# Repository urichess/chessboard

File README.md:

# chessboard

tests of chessboard using arduino + zephyr

Interesting links

Proyectos y tecnologías clave que te pueden ayudar
1. lichess-bot

https://github.com/lichess-bot-devs/lichess-bot

Un bot que se conecta a la API de Lichess y puede jugar partidas automáticamente.

Puedes modificarlo para que, en lugar de usar un motor de ajedrez, se comunique con tu hardware.

Es ideal como punto de partida para jugar partidas en Lichess a través de tu propio programa.

2. PySerial

https://pyserial.readthedocs.io/en/latest/pyserial.html#overview
Para comunicarte con tu tablero por USB (si usas un puerto serie virtual tipo /dev/ttyUSB0).

Puedes leer movimientos desde tu tablero y enviarle información como el movimiento del oponente.

3. Python-Chess
https://python-chess.readthedocs.io/en/latest/#
Excelente librería para manejar lógica de ajedrez (validar jugadas, FENs, PGNs).

Puedes usarla para comparar el estado del juego local con el de Lichess y traducir movimientos.

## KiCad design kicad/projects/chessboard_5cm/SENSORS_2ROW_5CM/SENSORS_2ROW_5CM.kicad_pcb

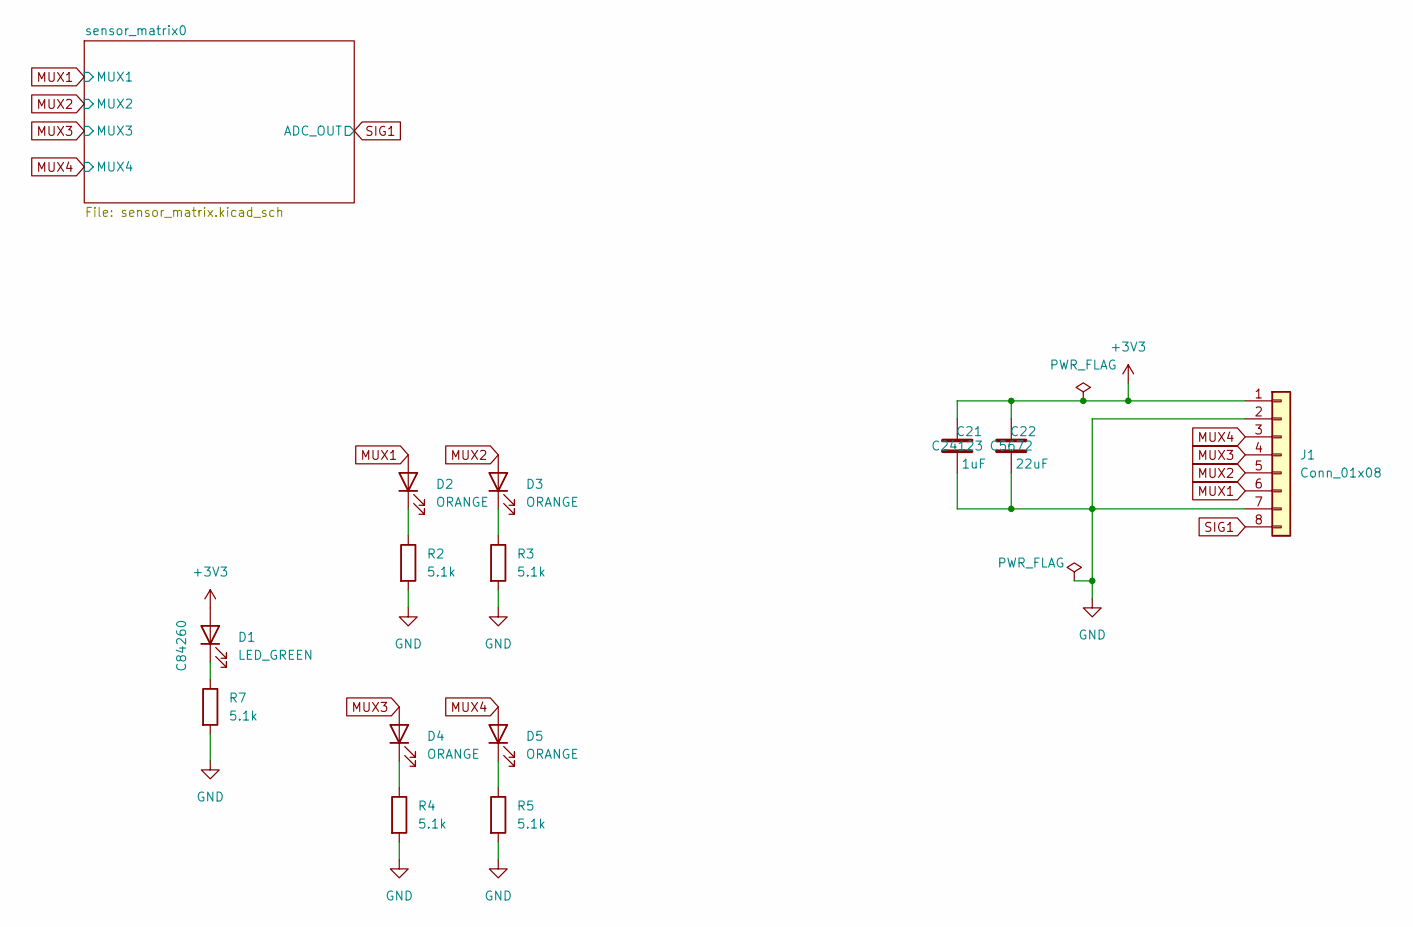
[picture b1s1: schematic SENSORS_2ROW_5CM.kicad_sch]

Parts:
C21: 1uF; C_0805_2012Metric_Pad1.18x1.45mm_HandSolder; LCSC p/n C24123
C22: 22uF; C_1206_3216Metric_Pad1.33x1.80mm_HandSolder; LCSC p/n C5672
D1: LED_GREEN; LED_0805_2012Metric_Pad1.15x1.40mm_HandSolder; LCSC p/n C84260
D2, D3, D4, D5: ORANGE; LED_0805_2012Metric_Pad1.15x1.40mm_HandSolder; LCSC p/n C434437
J1: Conn_01x08; PinHeader_1x08_P2.54mm_Horizontal; LCSC p/n C2894950
R2, R3, R4, R5, R7: 5.1k; R_0805_2012Metric_Pad1.20x1.40mm_HandSolder; LCSC p/n C84375

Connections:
+3V3: C21.1, C22.1, D1.2 (A), J1.1; also elsewhere on the board
GND: C21.2, C22.2, J1.2, J1.7, R2.2, R3.2, R4.2, R5.2, R7.2; also elsewhere on the board
MUX1: D2.2 (A), J1.6; also elsewhere on the board
MUX2: D3.2 (A), J1.5; also elsewhere on the board
MUX3: D4.2 (A), J1.4; also elsewhere on the board
MUX4: D5.2 (A), J1.3; also elsewhere on the board
unnamed: D1.1 (K), R7.1
unnamed: D2.1 (K), R2.1
unnamed: D3.1 (K), R3.1
unnamed: D4.1 (K), R4.1
unnamed: D5.1 (K), R5.1
SIG1: J1.8; also elsewhere on the board

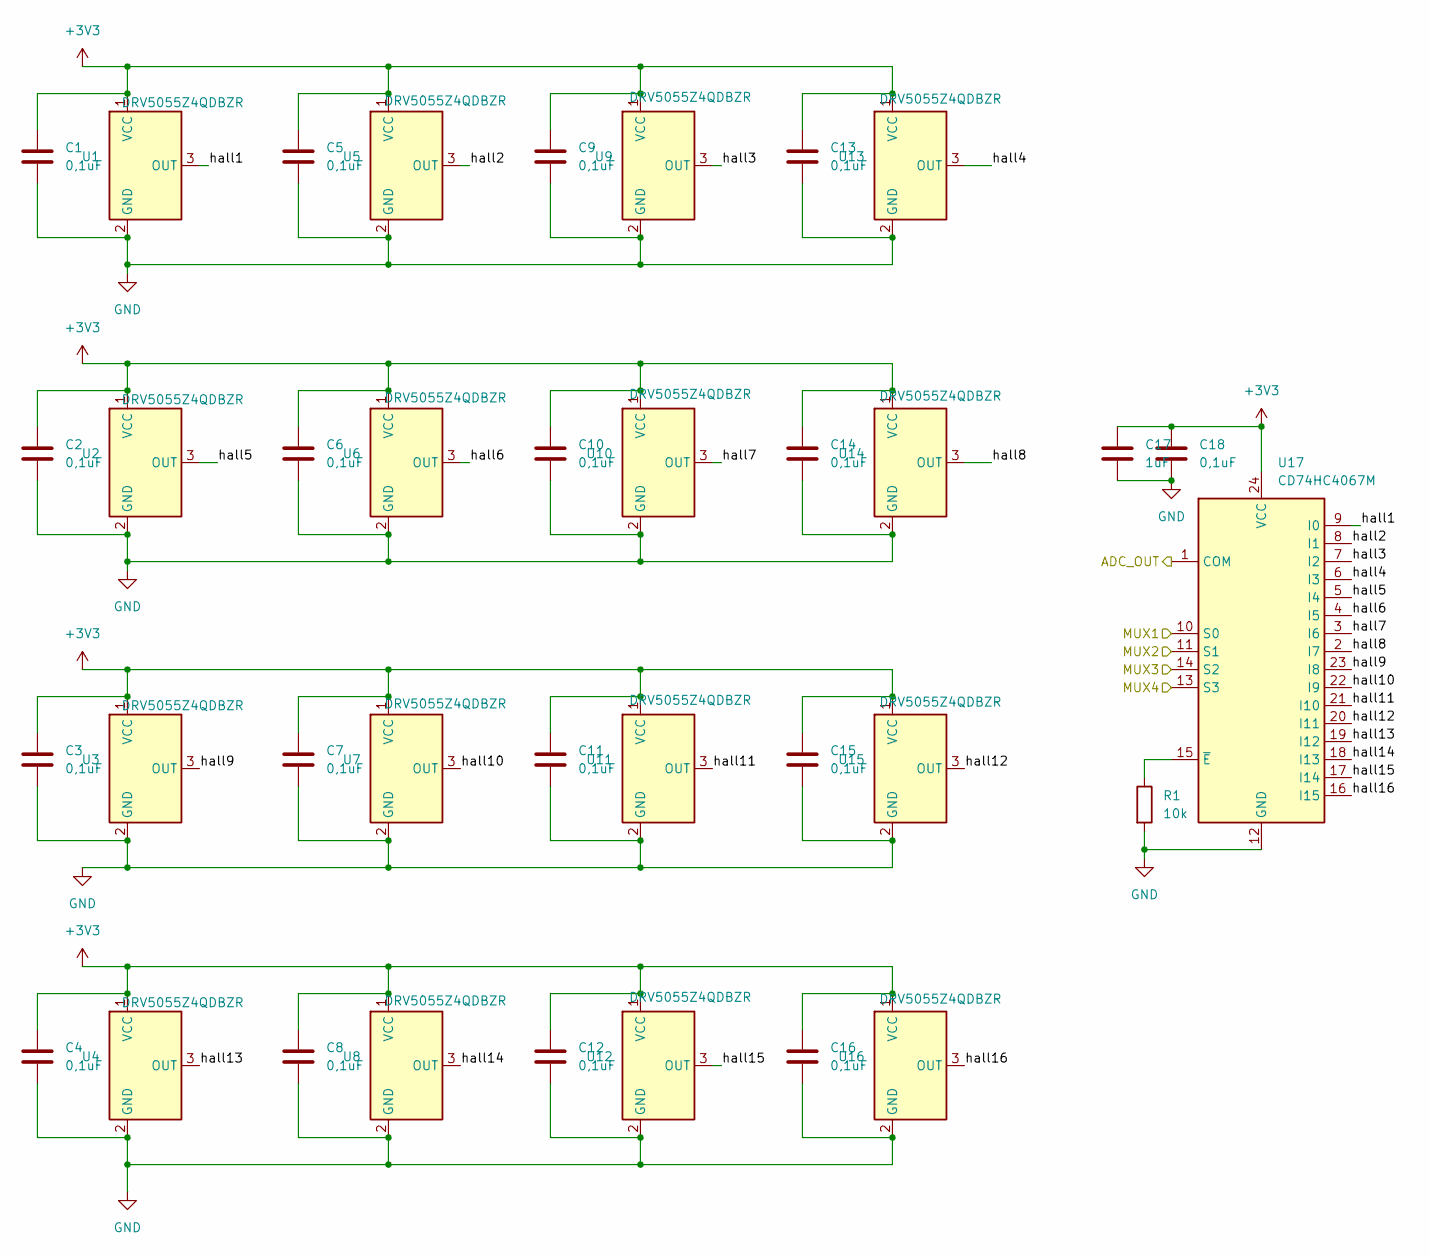
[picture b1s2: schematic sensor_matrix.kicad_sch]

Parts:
C1, C2, C3, C4, C5, C6, C7, C8, C9, C10, C11, C12, C13, C14, C15, C16, C18: 0,1uF; C_0805_2012Metric_Pad1.18x1.45mm_HandSolder; LCSC p/n C1711
C17: 1uF; C_0805_2012Metric_Pad1.18x1.45mm_HandSolder; LCSC p/n C24123
R1: 10k; R_0805_2012Metric_Pad1.20x1.40mm_HandSolder; LCSC p/n C84376
U1, U2, U3, U4, U5, U6, U7, U8, U9, U10, U11, U12, U13, U14, U15, U16: DRV5055Z4QDBZR; SOT-23_Handsoldering; LCSC p/n C2864477
U17: CD74HC4067M; SOIC-24W_7.5x15.4mm_P1.27mm; LCSC p/n C496123

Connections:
+3V3: C1.1, C2.1, C3.1, C4.1, C5.1, C6.1, C7.1, C8.1, C9.1, C10.1, C11.1, C12.1, C13.1, C14.1, C15.1, C16.1, C17.1, C18.1, U1.1 (VCC), U2.1 (VCC), U3.1 (VCC), U4.1 (VCC), U5.1 (VCC), U6.1 (VCC), U7.1 (VCC), U8.1 (VCC), U9.1 (VCC), U10.1 (VCC), U11.1 (VCC), U12.1 (VCC), U13.1 (VCC), U14.1 (VCC), U15.1 (VCC), U16.1 (VCC), U17.24 (VCC); also elsewhere on the board
/sensor_matrix0/hall1: U1.3 (OUT), U17.9 (I0)
/sensor_matrix0/hall2: U5.3 (OUT), U17.8 (I1)
/sensor_matrix0/hall3: U9.3 (OUT), U17.7 (I2)
/sensor_matrix0/hall4: U13.3 (OUT), U17.6 (I3)
/sensor_matrix0/hall5: U2.3 (OUT), U17.5 (I4)
/sensor_matrix0/hall6: U6.3 (OUT), U17.4 (I5)
/sensor_matrix0/hall7: U10.3 (OUT), U17.3 (I6)
/sensor_matrix0/hall8: U14.3 (OUT), U17.2 (I7)
/sensor_matrix0/hall9: U3.3 (OUT), U17.23 (I8)
/sensor_matrix0/hall10: U7.3 (OUT), U17.22 (I9)
/sensor_matrix0/hall11: U11.3 (OUT), U17.21 (I10)
/sensor_matrix0/hall12: U15.3 (OUT), U17.20 (I11)
/sensor_matrix0/hall13: U4.3 (OUT), U17.19 (I12)
/sensor_matrix0/hall14: U8.3 (OUT), U17.18 (I13)
/sensor_matrix0/hall15: U12.3 (OUT), U17.17 (I14)
/sensor_matrix0/hall16: U16.3 (OUT), U17.16 (I15)
GND: C1.2, C2.2, C3.2, C4.2, C5.2, C6.2, C7.2, C8.2, C9.2, C10.2, C11.2, C12.2, C13.2, C14.2, C15.2, C16.2, C17.2, C18.2, R1.2, U1.2 (GND), U2.2 (GND), U3.2 (GND), U4.2 (GND), U5.2 (GND), U6.2 (GND), U7.2 (GND), U8.2 (GND), U9.2 (GND), U10.2 (GND), U11.2 (GND), U12.2 (GND), U13.2 (GND), U14.2 (GND), U15.2 (GND), U16.2 (GND), U17.12 (GND); also elsewhere on the board
MUX1: U17.10 (S0); also elsewhere on the board
MUX2: U17.11 (S1); also elsewhere on the board
MUX3: U17.14 (S2); also elsewhere on the board
MUX4: U17.13 (S3); also elsewhere on the board
unnamed: R1.1, U17.15 (~E)
SIG1: U17.1 (COM); also elsewhere on the board

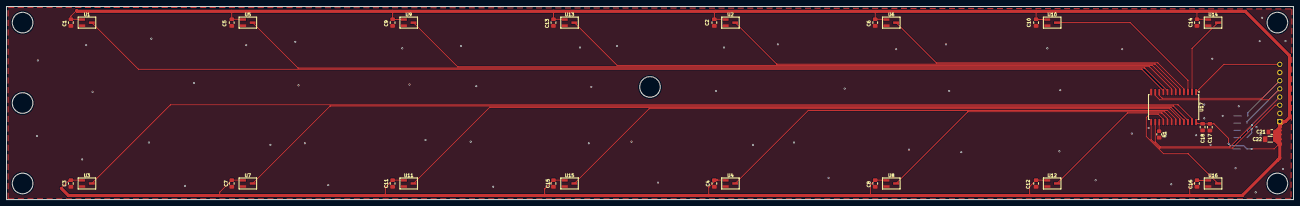
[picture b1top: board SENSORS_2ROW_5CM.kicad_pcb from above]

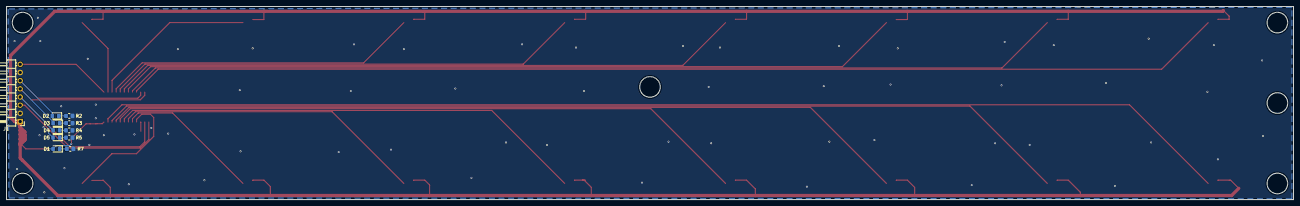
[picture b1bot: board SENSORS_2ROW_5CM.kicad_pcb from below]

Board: 2 copper layers, 400.0 x 60.0 mm, 49 parts (11 on the bottom side), 29 nets.

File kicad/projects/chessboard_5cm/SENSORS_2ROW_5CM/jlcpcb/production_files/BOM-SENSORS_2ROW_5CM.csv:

Comment,Designator,Footprint,LCSC,Quantity
"0,1uF","C1,C10,C11,C12,C13,C14,C15,C16,C18,C2,C3,C4,C5,C6,C7,C8,C9",C_0805_2012Metric_Pad1.18x1.45mm_HandSolder,C28233,17
10k,R1,R_0805_2012Metric_Pad1.20x1.40mm_HandSolder,C17414,1
1uF,"C17,C21",C_0805_2012Metric_Pad1.18x1.45mm_HandSolder,C28323,2
22uF,C22,C_1206_3216Metric_Pad1.33x1.80mm_HandSolder,C12891,1
5.1k,"R2,R3,R4,R5,R7",R_0805_2012Metric_Pad1.20x1.40mm_HandSolder,C27834,5
CD74HC4067M,U17,SOIC-24W_7.5x15.4mm_P1.27mm,C496123,1
DRV5055Z4QDBZR,"U1,U10,U11,U12,U13,U14,U15,U16,U2,U3,U4,U5,U6,U7,U8,U9",SOT-23_Handsoldering,C2864477,16
LED_GREEN,D1,LED_0805_2012Metric_Pad1.15x1.40mm_HandSolder,C2297,1
ORANGE,"D2,D3,D4,D5",LED_0805_2012Metric_Pad1.15x1.40mm_HandSolder,C2296,4
Conn_01x08,J1,PinHeader_1x08_P2.54mm_Horizontal,,1

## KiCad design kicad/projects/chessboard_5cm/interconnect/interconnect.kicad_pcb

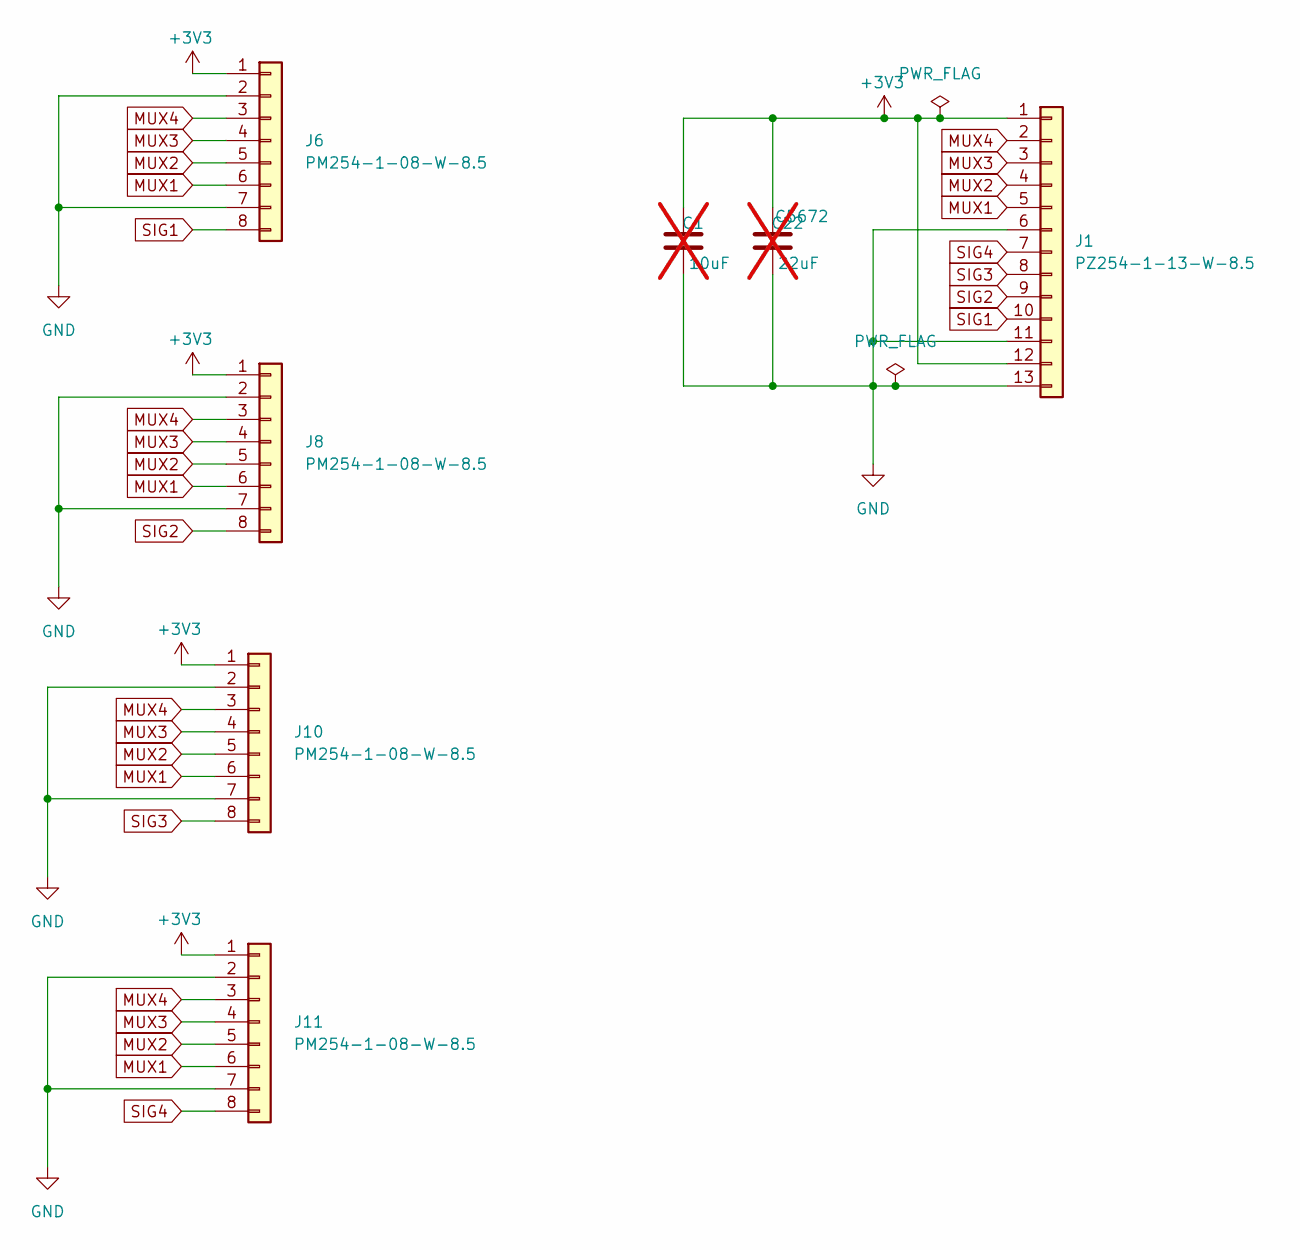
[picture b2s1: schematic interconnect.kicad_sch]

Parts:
C1: 10uF; C_1206_3216Metric_Pad1.33x1.80mm_HandSolder; not fitted
C22: 22uF; C_1206_3216Metric_Pad1.33x1.80mm_HandSolder; LCSC p/n C5672; not fitted
J1: PZ254-1-13-W-8.5; PinHeader_1x13_P2.54mm_Horizontal; LCSC p/n C2894955
J6, J8, J10, J11: PM254-1-08-W-8.5; PinSocket_1x08_P2.54mm_Horizontal; LCSC p/n C2897390

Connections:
+3V3: C1.1, C22.1, J1.1, J1.12, J6.1, J8.1, J10.1, J11.1
GND: C1.2, C22.2, J1.6, J1.11, J1.13, J6.2, J6.7, J8.2, J8.7, J10.2, J10.7, J11.2, J11.7
MUX1: J1.5, J6.6, J8.6, J10.6, J11.6
MUX2: J1.4, J6.5, J8.5, J10.5, J11.5
MUX3: J1.3, J6.4, J8.4, J10.4, J11.4
MUX4: J1.2, J6.3, J8.3, J10.3, J11.3
SIG1: J1.10, J6.8
SIG2: J1.9, J8.8
SIG3: J1.8, J10.8
SIG4: J1.7, J11.8

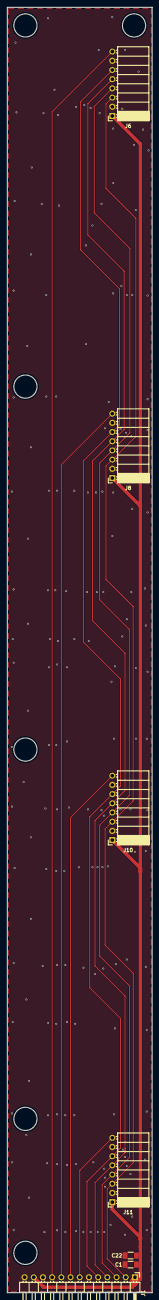
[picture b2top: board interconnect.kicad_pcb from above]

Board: 2 copper layers, 40.0 x 355.0 mm, 7 parts (0 on the bottom side), 10 nets.

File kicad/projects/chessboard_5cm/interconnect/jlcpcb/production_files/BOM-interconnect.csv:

Comment,Designator,Footprint,LCSC,Quantity
PM254-1-08-W-8.5,"J10,J11,J6,J8",PinSocket_1x08_P2.54mm_Horizontal,C2897390,4
PZ254-1-13-W-8.5,J1,PinHeader_1x13_P2.54mm_Horizontal,C2894955,1

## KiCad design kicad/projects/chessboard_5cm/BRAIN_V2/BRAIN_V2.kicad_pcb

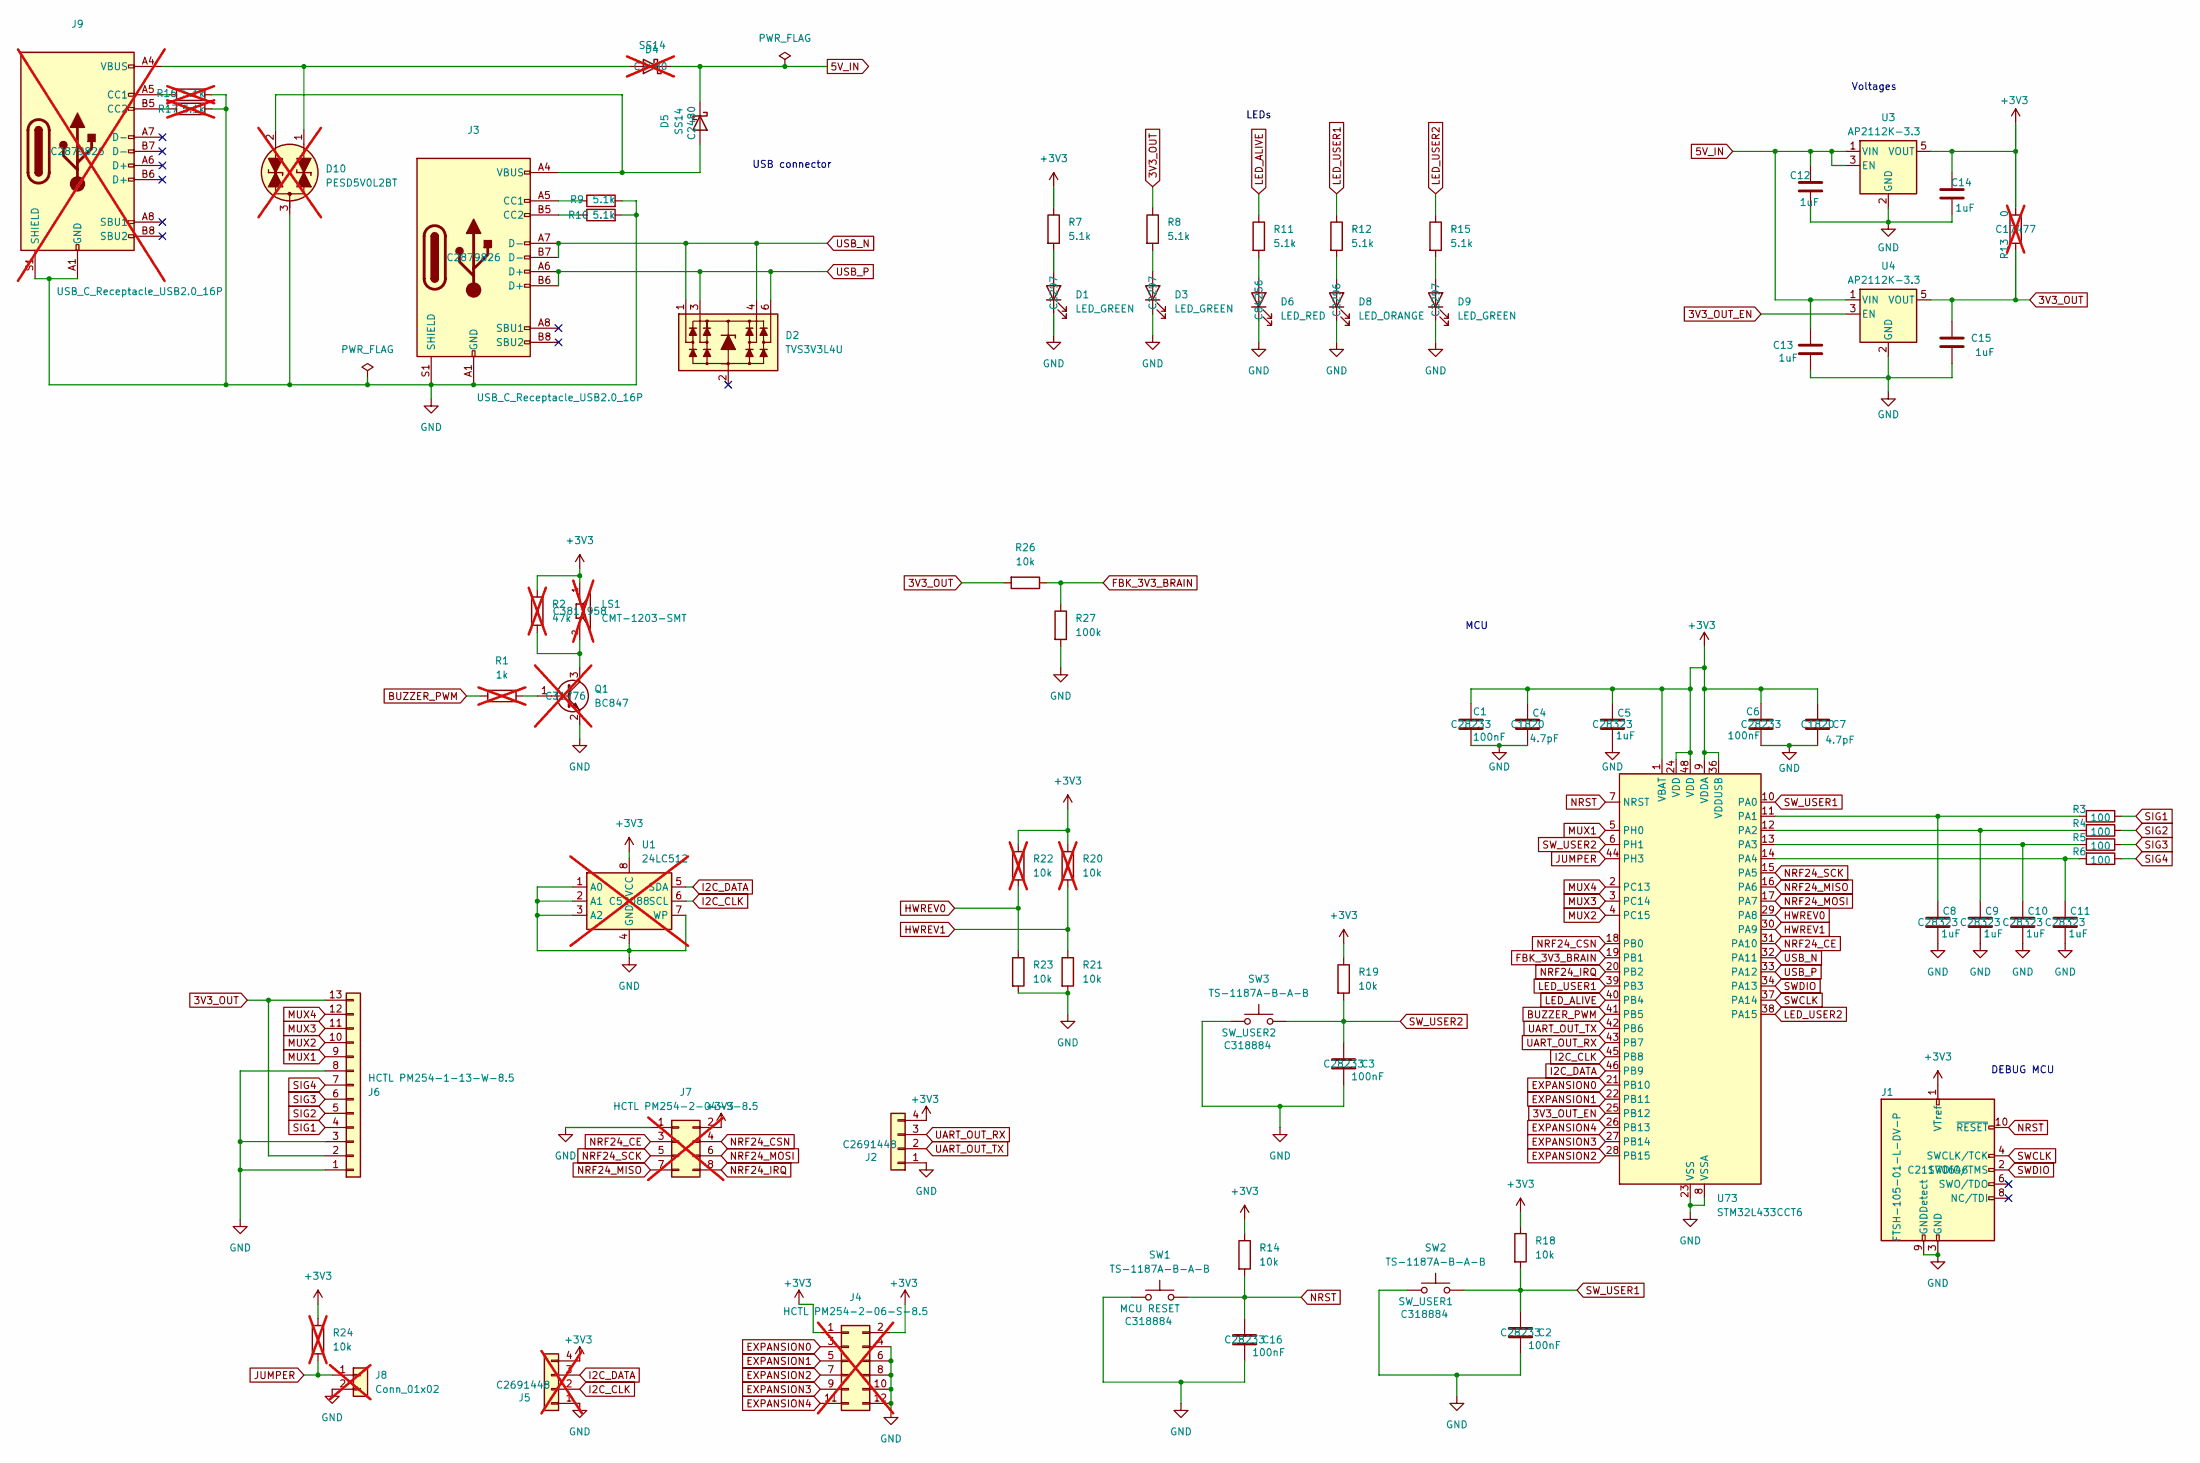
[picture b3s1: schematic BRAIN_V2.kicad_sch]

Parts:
C1, C2, C3, C6, C16: 100nF; C_0805_2012Metric_Pad1.18x1.45mm_HandSolder; LCSC p/n C28233
C4, C7: 4.7pF; C_0805_2012Metric_Pad1.18x1.45mm_HandSolder; LCSC p/n C1820
C5, C8, C9, C10, C11, C12, C13, C14, C15: 1uF; C_0805_2012Metric_Pad1.18x1.45mm_HandSolder; LCSC p/n C28323
D1, D3, D9: LED_GREEN; LED_0805_2012Metric_Pad1.15x1.40mm_HandSolder; LCSC p/n C2297
D2: TVS3V3L4U; TSOP-6_1.65x3.05mm_P0.95mm; LCSC p/n C28642315
D4: SS14; D_SMA; LCSC p/n C2480; not fitted
D5: SS14; D_SMA; LCSC p/n C2480
D6: LED_RED; LED_0805_2012Metric_Pad1.15x1.40mm_HandSolder; LCSC p/n C84256
D8: LED_ORANGE; LED_0805_2012Metric_Pad1.15x1.40mm_HandSolder; LCSC p/n C2296
D10: PESD5V0L2BT; SOT-23; LCSC p/n C12324; not fitted
J1: FTSH-105-01-L-DV-P; GCT_BD125-10-A-0305-0580-L-B; LCSC p/n C21170646
J2: C2691448; PinHeader_1x04_P2.54mm_Vertical; LCSC p/n C2691448
J3: USB_C_Receptacle_USB2.0_16P; USB_C_Receptacle_XKB_U262-16XN-4BVC11; LCSC p/n C2879826
J4: HCTL PM254-2-06-S-8.5; PinSocket_2x06_P2.54mm_Vertical_SMD; LCSC p/n C3975151; not fitted
J5: C2691448; PinHeader_1x04_P2.54mm_Vertical; LCSC p/n C2691448; not fitted
J6: HCTL PM254-1-13-W-8.5; PinSocket_1x13_P2.54mm_Horizontal; LCSC p/n C2897395
J7: HCTL PM254-2-04-S-8.5; PinSocket_2x04_P2.54mm_Vertical_SMD; LCSC p/n C3975149; not fitted
J8: Conn_01x02; PinHeader_1x02_P2.54mm_Vertical; LCSC p/n C492401; not fitted
J9: USB_C_Receptacle_USB2.0_16P; USB_C_Receptacle_XKB_U262-16XN-4BVC11; LCSC p/n C2879826; not fitted
LS1: CMT-1203-SMT; CUI_CMT-1203-SMT; PARTREV 1.01; LCSC p/n C3811958; not fitted
Q1: BC847; SOT-23; LCSC p/n C31776; not fitted
R1: 1k; R_0805_2012Metric_Pad1.20x1.40mm_HandSolder; LCSC p/n C17513; not fitted
R2: 47k; R_0805_2012Metric_Pad1.20x1.40mm_HandSolder; LCSC p/n C17713; not fitted
R3, R4, R5, R6: 100; R_0805_2012Metric_Pad1.20x1.40mm_HandSolder; LCSC p/n C17408
R7, R8, R9, R10, R11, R12, R15: 5.1k; R_0805_2012Metric_Pad1.20x1.40mm_HandSolder; LCSC p/n C27834
R13: 0; R_0805_2012Metric_Pad1.20x1.40mm_HandSolder; LCSC p/n C17477; not fitted
R14, R18, R19, R21, R23, R26: 10k; R_0805_2012Metric_Pad1.20x1.40mm_HandSolder; LCSC p/n C17414
R16, R17: 5.1k; R_0805_2012Metric_Pad1.20x1.40mm_HandSolder; LCSC p/n C27834; not fitted
R20, R22, R24: 10k; R_0805_2012Metric_Pad1.20x1.40mm_HandSolder; LCSC p/n C17414; not fitted
R27: 100k; R_0805_2012Metric_Pad1.20x1.40mm_HandSolder; LCSC p/n C25611
SW1, SW2, SW3: TS-1187A-B-A-B; SW_SPST_TL3342; LCSC p/n C318884
U1: 24LC512; SOIC-8_3.9x4.9mm_P1.27mm; LCSC p/n C52088; not fitted
U3, U4: AP2112K-3.3; SOT-23-5; LCSC p/n C23380830
U73: STM32L433CCT6; LQFP-48_7x7mm_P0.5mm; LCSC p/n C110061

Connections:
3V3_OUT: C15.1, J6.2, J6.13, R8.1, R13.1, R26.2, U4.5 (VOUT)
3V3_OUT_EN: U4.3 (EN), U73.25 (PB12)
5V_IN: C12.1, C13.1, D4.1 (K), D5.1 (K), U3.1 (VIN), U3.3 (EN), U4.1 (VIN)
+3V3: C1.1, C4.1, C5.1, C6.1, C7.1, C14.1, J1.1 (VTref), J2.4, J4.1, J4.2, J5.4, J7.2, LS1.1, R2.2, R7.1, R13.2, R14.1, R18.1, R19.1, R20.1, R22.1, R24.1, U1.8 (VCC), U3.5 (VOUT), U73.1 (VBAT), U73.9 (VDDA), U73.24 (VDD), U73.36 (VDDUSB), U73.48 (VDD)
BUZZER_PWM: R1.1, U73.41 (PB5)
EXPANSION0: J4.3, U73.21 (PB10)
EXPANSION1: J4.5, U73.22 (PB11)
EXPANSION2: J4.7, U73.28 (PB15)
EXPANSION3: J4.9, U73.27 (PB14)
EXPANSION4: J4.11, U73.26 (PB13)
FBK_3V3_BRAIN: R26.1, R27.1, U73.19 (PB1)
GND: C1.2, C2.1, C3.1, C4.2, C5.2, C6.2, C7.2, C8.2, C9.2, C10.2, C11.2, C12.2, C13.2, C14.2, C15.2, C16.1, D1.1 (K), D3.1 (K), D6.1 (K), D8.1 (K), D9.1 (K), D10.3 (Com), J1.3 (GND), J1.5 (GND), J1.9 (GNDDetect), J2.1, J3.A1 (GND), J3.A12 (GND), J3.B1 (GND), J3.B12 (GND), J3.S1 (SHIELD), J4.4, J4.6, J4.8, J4.10, J4.12, J5.1, J6.1, J6.3, J6.8, J7.1, J8.2, J9.A1 (GND), J9.A12 (GND), J9.B1 (GND), J9.B12 (GND), J9.S1 (SHIELD), Q1.2 (E), R9.2, R10.2, R16.2, R17.2, R21.2, R23.2, R27.2, SW1.1, SW2.1, SW3.1, U1.1 (A0), U1.2 (A1), U1.3 (A2), U1.4 (GND), U1.7 (WP), U3.2 (GND), U4.2 (GND), U73.8 (VSSA), U73.23 (VSS), U73.35 (VSS), U73.47 (VSS)
HWREV0: R22.2, R23.1, U73.29 (PA8)
HWREV1: R20.2, R21.1, U73.30 (PA9)
I2C_CLK: J5.2, U1.6 (SCL), U73.45 (PB8)
I2C_DATA: J5.3, U1.5 (SDA), U73.46 (PB9)
JUMPER: J8.1, R24.2, U73.44 (PH3)
LED_ALIVE: R11.1, U73.40 (PB4)
LED_USER1: R12.1, U73.39 (PB3)
LED_USER2: R15.1, U73.38 (PA15)
MUX1: J6.9, U73.5 (PH0)
MUX2: J6.10, U73.4 (PC15)
MUX3: J6.11, U73.3 (PC14)
MUX4: J6.12, U73.2 (PC13)
NRF24_CE: J7.3, U73.31 (PA10)
NRF24_CSN: J7.4, U73.18 (PB0)
NRF24_IRQ: J7.8, U73.20 (PB2)
NRF24_MISO: J7.7, U73.16 (PA6)
NRF24_MOSI: J7.6, U73.17 (PA7)
NRF24_SCK: J7.5, U73.15 (PA5)
NRST: C16.2, J1.10 (~RESET), R14.2, SW1.2, U73.7 (NRST)
unnamed: D1.2 (A), R7.2
unnamed: D3.2 (A), R8.2
unnamed: D6.2 (A), R11.2
unnamed: D8.2 (A), R12.2
unnamed: D9.2 (A), R15.2
unnamed: D4.2 (A), D10.1 (A1), J9.A4 (VBUS), J9.A9 (VBUS), J9.B4 (VBUS), J9.B9 (VBUS)
unnamed: D5.2 (A), D10.2 (A2), J3.A4 (VBUS), J3.A9 (VBUS), J3.B4 (VBUS), J3.B9 (VBUS)
unnamed: J3.A5 (CC1), R9.1
unnamed: J3.B5 (CC2), R10.1
unnamed: J9.A5 (CC1), R16.1
unnamed: J9.B5 (CC2), R17.1
unnamed: Q1.1 (B), R1.2
unnamed: LS1.2, Q1.3 (C), R2.1
unnamed: C8.1, R3.2, U73.11 (PA1)
unnamed: C9.1, R4.2, U73.12 (PA2)
unnamed: C10.1, R5.2, U73.13 (PA3)
unnamed: C11.1, R6.2, U73.14 (PA4)
SIG1: J6.4, R3.1
SIG2: J6.5, R4.1
SIG3: J6.6, R5.1
SIG4: J6.7, R6.1
SWCLK: J1.4 (SWCLK/TCK), U73.37 (PA14)
SWDIO: J1.2 (SWDIO/TMS), U73.34 (PA13)
SW_USER1: C2.2, R18.2, SW2.2, U73.10 (PA0)
SW_USER2: C3.2, R19.2, SW3.2, U73.6 (PH1)
UART_OUT_RX: J2.3, U73.43 (PB7)
UART_OUT_TX: J2.2, U73.42 (PB6)
USB_N: D2.1 (L1), D2.4 (L3), J3.A7 (D-), J3.B7 (D-), U73.32 (PA11)
USB_P: D2.3 (L2), D2.6 (L4), J3.A6 (D+), J3.B6 (D+), U73.33 (PA12)

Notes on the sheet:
LEDs
USB connector
Voltages
DEBUG MCU
MCU

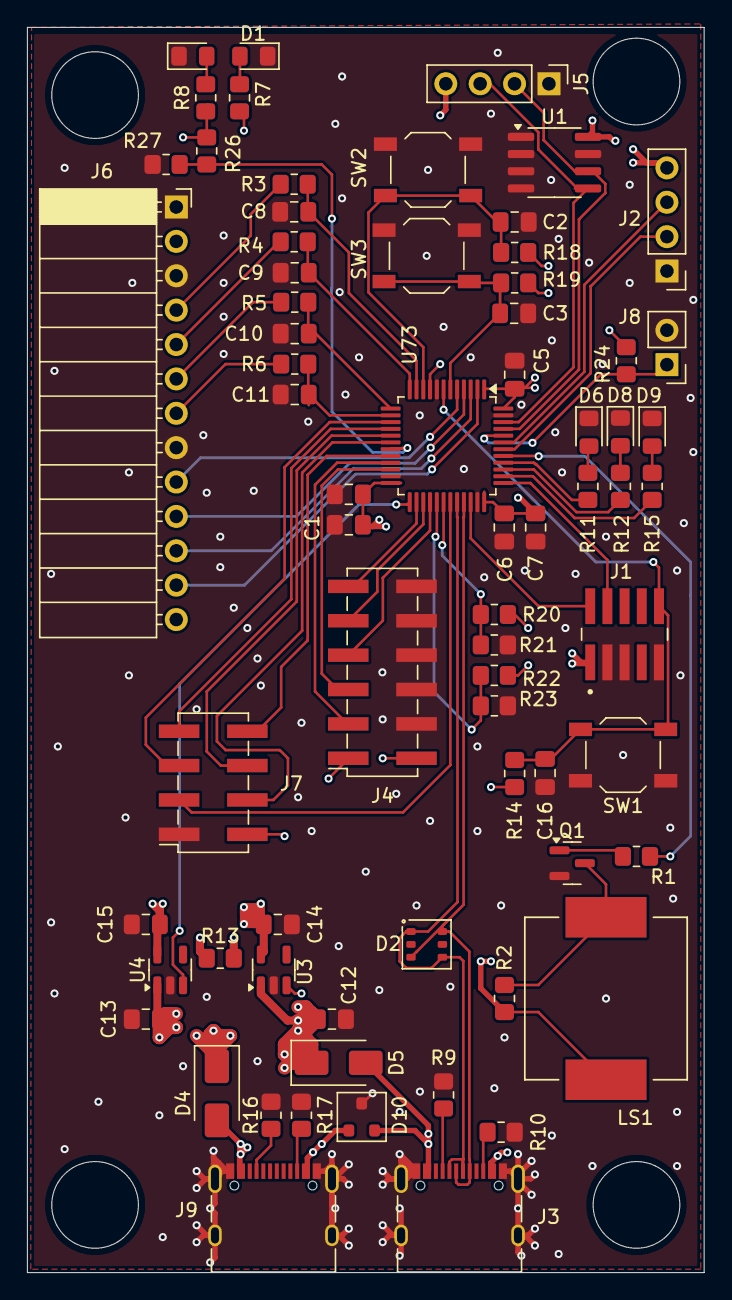
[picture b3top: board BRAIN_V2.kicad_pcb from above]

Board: 4 copper layers, 50.0 x 92.0 mm, 69 parts (0 on the bottom side), 60 nets.

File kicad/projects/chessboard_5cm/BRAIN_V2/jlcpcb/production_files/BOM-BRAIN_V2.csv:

Comment,Designator,Footprint,LCSC,Quantity
100,"R3,R4,R5,R6",R_0805_2012Metric_Pad1.20x1.40mm_HandSolder,C17408,4
100k,R27,R_0805_2012Metric_Pad1.20x1.40mm_HandSolder,C149504,1
100nF,"C1,C16,C2,C3,C6",C_0805_2012Metric_Pad1.18x1.45mm_HandSolder,C28233,5
10k,"R14,R18,R19,R21,R23,R26",R_0805_2012Metric_Pad1.20x1.40mm_HandSolder,C17414,6
1uF,"C10,C11,C12,C13,C14,C15,C5,C8,C9",C_0805_2012Metric_Pad1.18x1.45mm_HandSolder,C28323,9
4.7pF,"C4,C7",C_0805_2012Metric_Pad1.18x1.45mm_HandSolder,C1820,2
5.1k,"R10,R11,R12,R15,R16,R17,R7,R8,R9",R_0805_2012Metric_Pad1.20x1.40mm_HandSolder,C27834,9
AP2112K-3.3,"U3,U4",SOT-23-5,C23380830,2
C2691448,J2,PinHeader_1x04_P2.54mm_Vertical,C2691448,1
FTSH-105-01-L-DV-P,J1,GCT_BD125-10-A-0305-0580-L-B,C21170646,1
HCTL PM254-1-13-W-8.5,J6,PinSocket_1x13_P2.54mm_Horizontal,C2897395,1
LED_GREEN,"D1,D3,D9",LED_0805_2012Metric_Pad1.15x1.40mm_HandSolder,C2297,3
LED_ORANGE,D8,LED_0805_2012Metric_Pad1.15x1.40mm_HandSolder,C2296,1
LED_RED,D6,LED_0805_2012Metric_Pad1.15x1.40mm_HandSolder,C84256,1
SS14,D5,D_SMA,C2480,1
STM32L433CCT6,U73,LQFP-48_7x7mm_P0.5mm,C110061,1
TS-1187A-B-A-B,"SW1,SW2,SW3",SW_SPST_TL3342,C318884,3
TVS3V3L4U,D2,TSOP-6_1.65x3.05mm_P0.95mm,C28642315,1
USB_C_Receptacle_USB2.0_16P,J3,USB_C_Receptacle_XKB_U262-16XN-4BVC11,C2879826,1
